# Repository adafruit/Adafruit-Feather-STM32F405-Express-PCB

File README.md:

## Adafruit Adafruit Feather STM32F405 Express PCB

<a href="http://www.adafruit.com/products/4382"><br/>
Click here to purchase one from the Adafruit shop</a>

PCB files for the Adafruit Adafruit Feather STM32F405 Express. 

Format is EagleCAD schematic and board layout
* https://www.adafruit.com/product/4382

### Description

ST takes flight in this upcoming Feather board. The new STM32F405 Feather (video) that we designed runs CircuitPython at a blistering 168MHz – our fastest CircuitPython board ever! We put a STEMMA QT / Qwiic port on the end, so you can really easily plug and play I2C sensors.

This Feather has lots of goodies:

* STM32F405 Cortex M4 with FPU and 1MB Flash, 168MHz speed
* 192KB RAM total - 128 KB RAM for general usage + 64 KB program-only/cache RAM
* 3.3V logic, but almost all pins are 5V compliant!
* USB C power and data - our first USB C Feather!
* LiPo connector and charger
* SD socket on the bottom, connected to SDIO port
* 2 MB SPI Flash chip
* Built in NeoPixel indicator
* I2C, UART, GPIO, ADCs, DACs
* Qwiic/STEMMA-QT connector for fast I2C connectivity
* We use the built-in USB DFU bootloader to load firmware. It does not come with a UF2 bootloader.

With CircuitPython basics running on this board, it's fast to get all our drivers working, then use the built in plotter in Mu to instantly get sensor data displaying within 3 minutes of unboxing.

You can use MicroPython, CircuitPython or Arduino IDE with this board, with some caveats. This board and chipset is new so expect rapid developments and updates!

* CircuitPython support is under development. We have digital IO, analog in/out, I2C, SPI, PWM working so far and more on the way. For example, the SDIO SD card is not yet supported natively. DisplayIO is also not yet supported.
* Arduino is supported through STM32duino. There's no auto-reset bootloader support yet so you have to pull the BOOT0 pin high and manually reset before uploading. That said, STM32 support is really good, and we were able to run just about every sketch we tried.
* MicroPython support is very solid but Adafruit does not provide MicroPython libraries for sensors!

We tested this in Arduino STM32duino with all our FeatherWings and only the RFM69/RFM9x libraries did not work (they are very platform specific). Its an extraordinarily fast Feather, and our first foray into STM32 - very exciting!

### License

Adafruit invests time and resources providing this open source design, please support Adafruit and open-source hardware by purchasing products from [Adafruit](https://www.adafruit.com)!

Designed by Limor Fried/Ladyada for Adafruit Industries.

Creative Commons Attribution/Share-Alike, all text above must be included in any redistribution. 
See license.txt for additional details.

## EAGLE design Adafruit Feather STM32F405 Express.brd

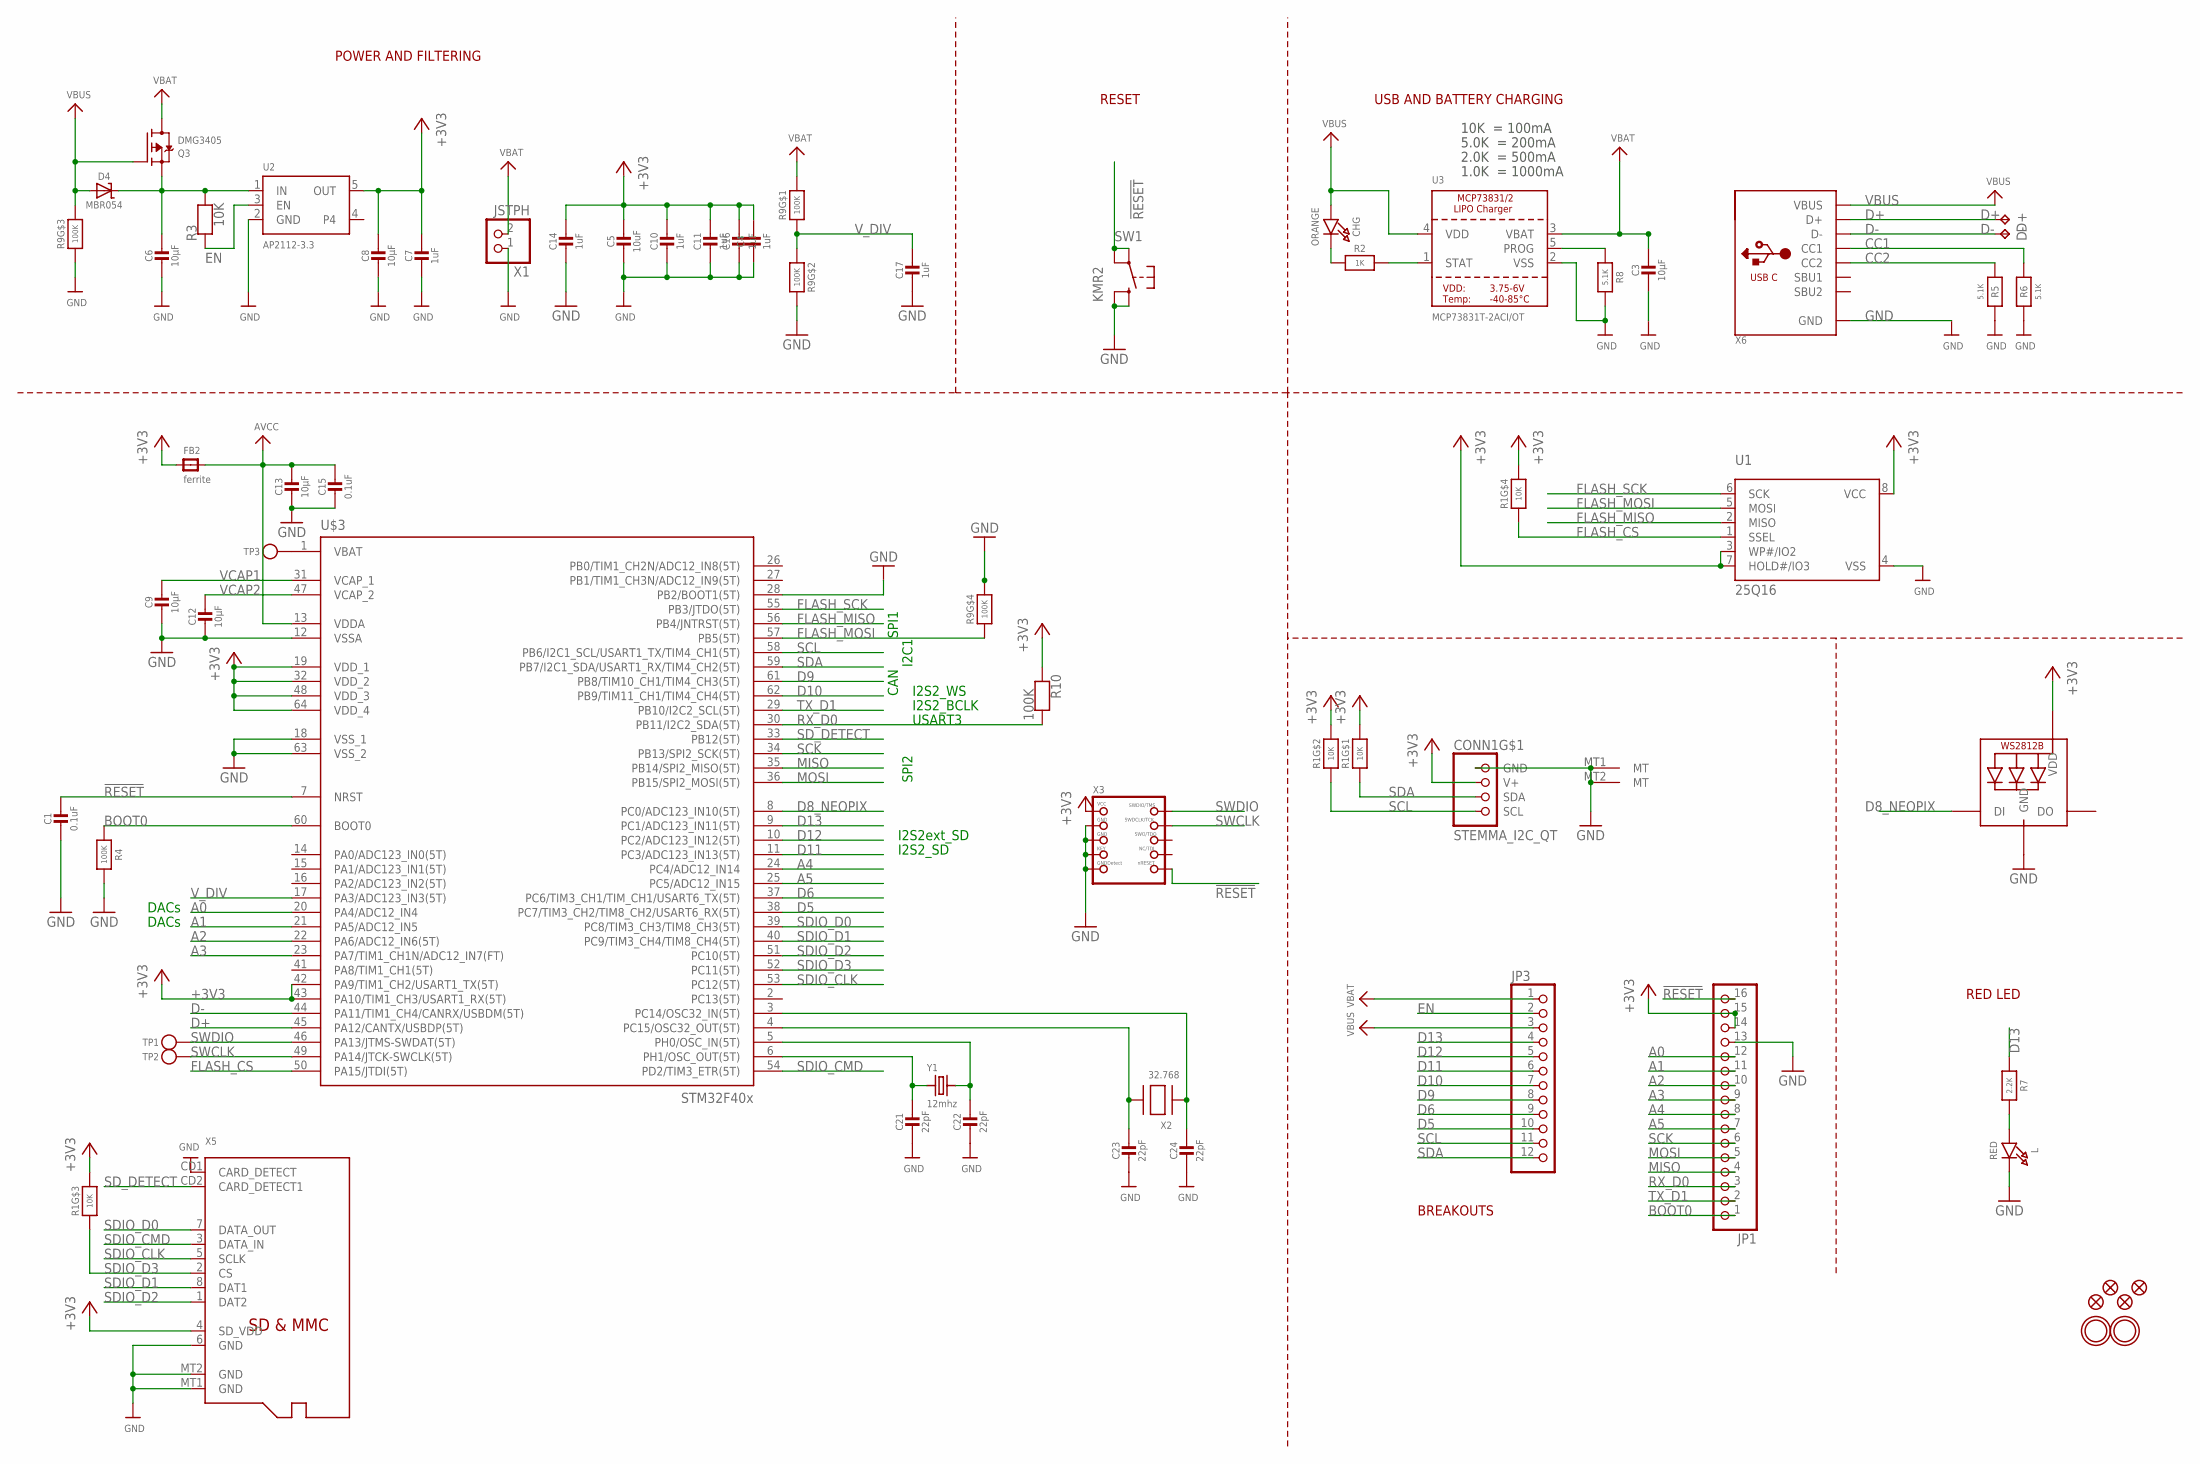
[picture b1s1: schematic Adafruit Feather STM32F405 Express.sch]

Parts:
C1, C15: 0.1uF; 0603-NO
C2: 22pF; RESPACK_4X0603
C3, C6, C8, C9, C12, C13: 10µF; 0805-NO
C4, C7, C10, C11, C14, C16, C17: 1uF; 0603-NO
C5: 10uF; 0805-NO
CHG: ORANGE; CHIPLED_0805_NOOUTLINE
CONN1: STEMMA_I2C_QT; JST_SH4
D4: MBR054; SOD-123
D+: TPB1,27; B1,27
D-: TPB1,27; B1,27
FB2: ferrite; 0805-NO
JP1: HEADER-1X16ROUND; 1X16_ROUND
JP3: HEADER-1X12; 1X12_ROUND
L: RED; CHIPLED_0805_NOOUTLINE
LED1: WS2812B3535; LED3535
Q3: DMG3405; SOT23-R
R1: 10K; RESPACK_4X0603_NO
R2: 1K; 0603-NO
R3: 10K; 0603-NO
R4, R10: 100K; 0603-NO
R5, R6, R8: 5.1K; 0603-NO
R7: 2.2K; 0603-NO
R9: 100K; RESPACK_4X0603_NO
SW1: KMR2; BTN_KMR2_4.6X2.8
TP1, TP2, TP3: TESTPOINTROUND1.5MM; TESTPOINT_ROUND_1.5MM
U1: 25Q16; SOIC8_150MIL
U2: AP2112-3.3; SOT23-5
U3: MCP73831T-2ACI/OT; SOT23-5
U$3: STM32F405R; TQFP64
U$5, U$34, U$35, U$37: FIDUCIAL_1MM
U$31, U$32: MOUNTINGHOLE2.5; MOUNTINGHOLE_2.5_PLATED
X1: JSTPH; JSTPH2
X2: 32.768; XTAL3215
X3: JTAG-CORTEX; 2X05_1.27MM_SMT
X5: MICROSD
X6: USB_C; USB_C_CUSB31-CFM2AX-01-X
Y1: 12mhz; CRYSTAL_2.5X2

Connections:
!RESET: C1.1, JP1.16, SW1.A, SW1.A' (P1), U$3.7 (NRST), X3.10 (NRESET)
+3V3: C4.1, C5.1, C7.1, C8.1, C10.1, C11.1, C14.1, C16.1, CONN1.2 (V+), FB2.1, JP1.14, JP1.15, LED1.2 (VDD), R1.5 (2), R1.6 (2), R1.7 (2), R1.8 (2), R10.1, U1.3 (WP#/IO2), U1.7 (HOLD#/IO3), U1.8 (VCC), U2.5 (OUT), U$3.19 (VDD_1), U$3.32 (VDD_2), U$3.42 (PA9/TIM1_CH2/USART1_TX(5T)), U$3.43 (PA10/TIM1_CH3/USART1_RX(5T)), U$3.48 (VDD_3), U$3.64 (VDD_4), X3.1 (VCC), X5.4 (SD_VDD)
A0: JP1.12, U$3.20 (PA4/ADC12_IN4)
A1: JP1.11, U$3.21 (PA5/ADC12_IN5)
A2: JP1.10, U$3.22 (PA6/ADC12_IN6(5T))
A3: JP1.9, U$3.23 (PA7/TIM1_CH1N/ADC12_IN7(FT))
A4: JP1.8, U$3.24 (PC4/ADC12_IN14)
A5: JP1.7, U$3.25 (PC5/ADC12_IN15)
AVCC: C13.1, C15.1, FB2.2, U$3.13 (VDDA)
BATTERY: TP3.P$1, U$3.1 (VBAT)
BOOT0: JP1.1, R4.1, U$3.60 (BOOT0)
CC1: R6.2, X6.A5 (CC1)
CC2: R5.2, X6.B5 (CC2)
D5: JP3.10, U$3.38 (PC7/TIM3_CH2/TIM8_CH2/USART6_RX(5T))
D6: JP3.9, U$3.37 (PC6/TIM3_CH1/TIM_CH1/USART6_TX(5T))
D8_NEOPIX: LED1.1 (DI), U$3.8 (PC0/ADC123_IN10(5T))
D9: JP3.8, U$3.61 (PB8/TIM10_CH1/TIM4_CH3(5T))
D10: JP3.7, U$3.62 (PB9/TIM11_CH1/TIM4_CH4(5T))
D11: JP3.6, U$3.11 (PC3/ADC123_IN13(5T))
D12: JP3.5, U$3.10 (PC2/ADC123_IN12(5T))
D13: JP3.4, R7.1, U$3.9 (PC1/ADC123_IN11(5T))
D+: D+.TP, U$3.45 (PA12/CANTX/USBDP(5T)), X6.A6 (D+), X6.B6 (D+)
D-: D-.TP, U$3.44 (PA11/TIM1_CH4/CANRX/USBDM(5T)), X6.A7 (D-), X6.B7 (D-)
EN: JP3.2, R3.1, U2.3 (EN)
FLASH_CS: R1.4 (1), U1.1 (SSEL), U$3.50 (PA15/JTDI(5T))
FLASH_MISO: U1.2 (MISO), U$3.56 (PB4/JNTRST(5T))
FLASH_MOSI: R9.4 (1), U1.5 (MOSI), U$3.57 (PB5(5T))
FLASH_SCK: U1.6 (SCK), U$3.55 (PB3/JTDO(5T))
GND: C1.2, C2.5 (2), C2.6 (2), C2.7 (2), C2.8 (2), C3.2, C4.2, C5.2, C6.2, C7.2, C8.2, C9.2, C10.2, C11.2, C12.2, C13.2, C14.2, C15.2, C16.2, C17.2, CONN1.1 (GND), CONN1.MT1 (MT), CONN1.MT2 (MT), JP1.13, L.C, LED1.4 (GND), R4.2, R5.1, R6.1, R8.2, R9.3 (1), R9.5 (2), R9.7 (2), SW1.B (S), SW1.B' (S1), U1.4 (VSS), U2.2 (GND), U3.2 (VSS), U$3.12 (VSSA), U$3.18 (VSS_1), U$3.28 (PB2/BOOT1(5T)), U$3.63 (VSS_2), X1.1, X3.3 (GND), X3.5 (GND), X3.7 (KEY), X3.9 (GNDDETECT), X5.6 (GND), X5.CD1 (CARD_DETECT), X5.MT1 (GND), X5.MT2 (GND), X6.A1B12 (GND), X6.B1A12 (GND)
MISO: JP1.4, U$3.35 (PB14/SPI2_MISO(5T))
MOSI: JP1.5, U$3.36 (PB15/SPI2_MOSI(5T))
unnamed: CHG.C, R2.1
unnamed: L.A, R7.2
unnamed: R2.2, U3.1 (STAT)
unnamed: R8.1, U3.5 (PROG)
unnamed: C2.4 (1), U$3.3 (PC14/OSC32_IN(5T)), X2.P$1
unnamed: C2.2 (1), U$3.5 (PH0/OSC_IN(5T)), Y1.3 (2)
unnamed: C2.3 (1), U$3.4 (PC15/OSC32_OUT(5T)), X2.P$2
unnamed: C2.1, U$3.6 (PH1/OSC_OUT(5T)), Y1.1
RX_D0: JP1.3, R10.2, U$3.30 (PB11/I2C2_SDA(5T))
SCK: JP1.6, U$3.34 (PB13/SPI2_SCK(5T))
SCL: CONN1.4 (SCL), JP3.11, R1.2 (1), U$3.58 (PB6/I2C1_SCL/USART1_TX/TIM4_CH1(5T))
SDA: CONN1.3 (SDA), JP3.12, R1.1, U$3.59 (PB7/I2C1_SDA/USART1_RX/TIM4_CH2(5T))
SDIO_CLK: U$3.53 (PC12(5T)), X5.5 (SCLK)
SDIO_CMD: U$3.54 (PD2/TIM3_ETR(5T)), X5.3 (DATA_IN)
SDIO_D0: U$3.39 (PC8/TIM3_CH3/TIM8_CH3(5T)), X5.7 (DATA_OUT)
SDIO_D1: U$3.40 (PC9/TIM3_CH4/TIM8_CH4(5T)), X5.8 (DAT1)
SDIO_D2: U$3.51 (PC10(5T)), X5.1 (DAT2)
SDIO_D3: R1.3 (1), U$3.52 (PC11(5T)), X5.2 (CS)
SD_DETECT: U$3.33 (PB12(5T)), X5.CD2 (CARD_DETECT1)
SWCLK: TP2.P$1, U$3.49 (PA14/JTCK-SWCLK(5T)), X3.4 (SWDCLK)
SWDIO: TP1.P$1, U$3.46 (PA13/JTMS-SWDAT(5T)), X3.2 (SWDIO)
TX_D1: JP1.2, U$3.29 (PB10/I2C2_SCL(5T))
VBAT: C3.1, JP3.1, Q3.3 (D), R9.8 (2), U3.3 (VBAT), X1.2
VBUS: CHG.A, D4.A, JP3.3, Q3.1 (G), R9.6 (2), U3.4 (VDD), X6.A4B9 (VBUS), X6.B4A9 (VBUS)
VCAP1: C9.1, U$3.31 (VCAP_1)
VCAP2: C12.1, U$3.47 (VCAP_2)
VHI: C6.1, D4.C, Q3.2 (S), R3.2, U2.1 (IN)
V_DIV: C17.1, R9.1, R9.2 (1), U$3.17 (PA3/ADC123_IN3(5T))

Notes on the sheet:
POWER AND FILTERING
RESET
10K = 100mA
5.0K = 200mA
2.0K = 500mA
1.0K = 1000mA
USB AND BATTERY CHARGING
BREAKOUTS
RED LED
SPI1
SPI2
USART3
DACs
I2C1
I2S2_WS
I2S2_BCLK
I2S2_SD
I2S2ext_SD
CAN

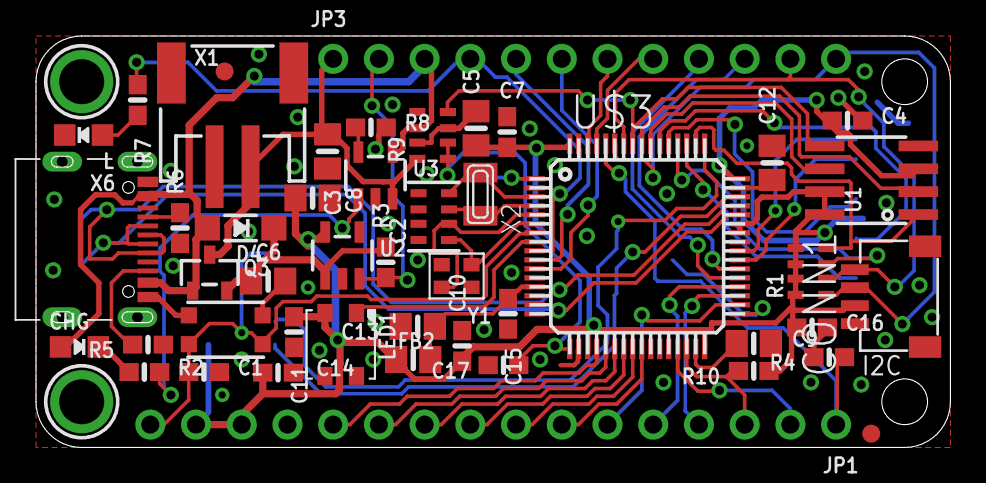
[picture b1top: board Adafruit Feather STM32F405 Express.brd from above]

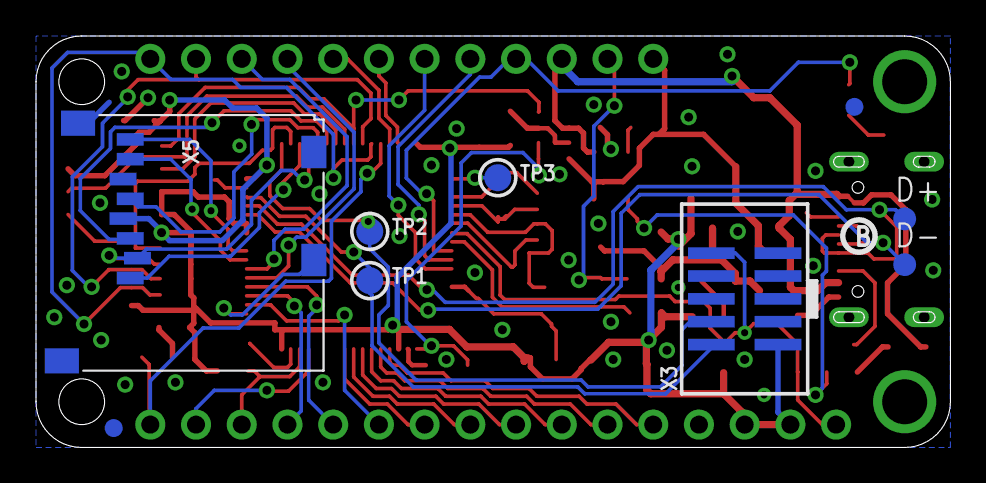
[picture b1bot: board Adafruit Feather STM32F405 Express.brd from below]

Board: 2 copper layers, 50.8 x 22.9 mm, 61 parts (11 on the bottom side), 59 nets.

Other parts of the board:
U$13: PCBFEAT-REV-040
U$24: FEATHER_STM32F405_TOP
U$40: FEATHER_STM32F405_BOT

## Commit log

2020-01-17 Adding board files.

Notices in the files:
parts and their libraries:
microbuilder: This work is placed in the public domain, and may be freely used for commercial and non-commercial work with the following conditions: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
